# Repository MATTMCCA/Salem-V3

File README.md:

# Salem Version 3

Third Revision of Salem, Capacitive Proximity Sensor.

https://youtu.be/Kz70OKQegTU

---

### Salem was originally designed as a REM Pod competitor. A conscience and lack of follow-though drove me to release the project, for the betterment of *Parapsychology Research*.

(Plus I didn't feel like dealing with *FCC Regulatory Compliance*.... or shipping logistics, customers, pricing, manufacturing, overhead... )

Effective range, depending on placement can vary from 6-10 inches. This is a ballpark estimate from lab testing. I have not had time to carry out a conclusive test to gauge the effective sensing range.

---

### Info

This project is a battery powered capacitive proximity sensor. Some folks believe a device like this will detect paranormal apparitions. **I can not confirm or deny the existence of ghosts. I am also not claiming this device will detect paranormal apparitions, this includes but is not limited too.**

- The Jersey Devil
- The Headless Body of Spiro Agnew
- Ghost
- Demons / Angles
- Batman
- Karma
- UFO's / USO's
- The Chupacabra
- Vampires
- Witches / Wizards
- The SOB that ate my Twix
- Bigfoot / Yeti's
- Tom Cruise
- Most Breads of Cats.
- Bloody Mary
- Unicorns
- Other Benign and Nefarious Mythical Creatures

However devices like this do exist on the market, and consumers use them in an effort to detect the "paranormal".

In full transparency, both the hardware and firmware are included in this repo. Should an individual wish to understand the operation of this device and similar devices, all necessary information is provided.

### Operation Note:

[Further Readings A](https://www.allaboutcircuits.com/technical-articles/introduction-to-capacitive-touch-sensing)

[Further Readings B](https://www.clippercontrols.com/pages/Dielectric-Constant-Values.html)

**I offer no support for this device, it has become a leisurely project.**

---

This project has been added to the hackaday [halloween hackfest](https://hackaday.com/2021/08/10/new-contest-halloween-hackfest/)

### Borrowed works maintain original license.

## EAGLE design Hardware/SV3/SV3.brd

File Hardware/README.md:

# Hardware Assembly 

The following items were purchased to aid in physical assembly.

- [Mounting Tape](https://www.amazon.com/gp/product/B0888DKR92)
- [Stainless Steel Internal Tooth Star Lock Washers](https://www.amazon.com/gp/product/B0794YF3QP/)
- [M3 Stainless Steel 304 Hex Socket Head Cap Bolt](https://www.amazon.com/gp/product/B07VNDFYNQ/)

## Assembly Notes

- `40mm` of `0.5mm x 24mm` mounting tape was used to adhere the battery pack onto the PCB before soldering the battery pack leads.
- `1 M3, lock washer` was placed on the antenna pad
- `1 M3, 5mm bolt` was passed though the lock washer, though the PCB, and screwed into the taped `M3 antenna`.

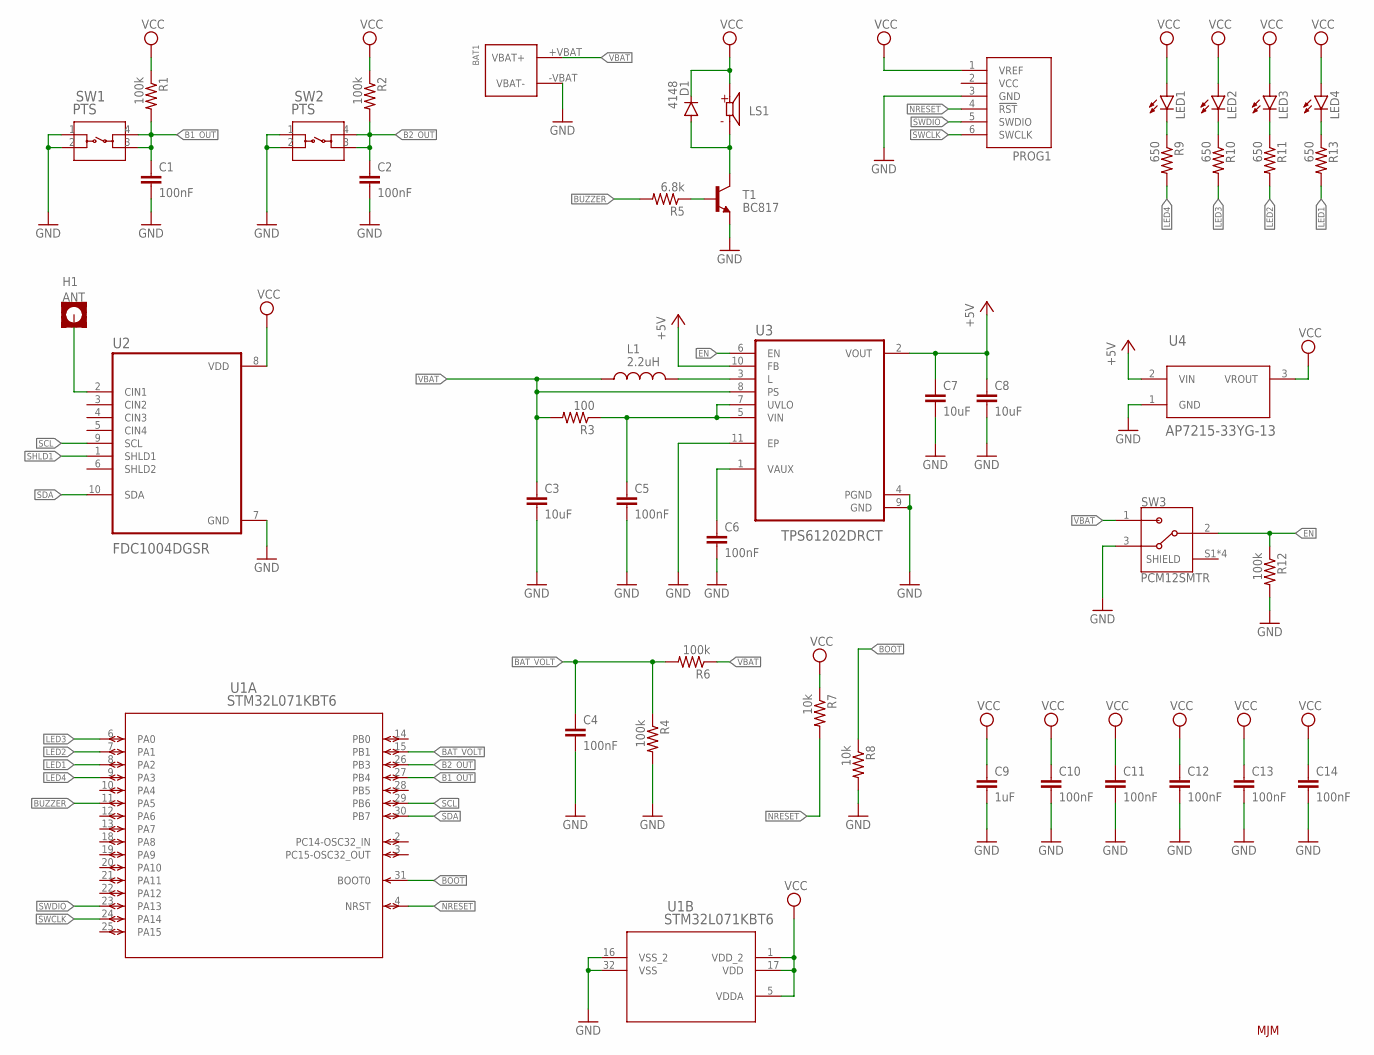
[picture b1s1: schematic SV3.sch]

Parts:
BAT1: 2462_NO_HOLES; 2462_NO-MOUNTING-HOLES
C1, C2, C4, C5, C6, C10, C11, C12, C13, C14: 100nF; C0603
C3, C7, C8: 10uF; C0805
C9: 1uF; C0603
D1: 4148; SOD80C
H1: ANT; 3,3-PAD-SQUARE
L1: 2.2uH; IND_LQH2HPZ2R2MJRL
LED1, LED2, LED3, LED4: LEDCHIPLED_0805; CHIPLED_0805
LS1: CSS-0575A-SMT; CUI_CSS-0575A-SMT
PROG1: 0532610671
R1, R2, R4, R6, R12: 100k; R0603
R3: 100; R0603
R5: 6.8k; R0603
R7, R8: 10k; R0603
R9, R10, R11, R13: 650; R0603
SW1, SW2: PTS; PTS_647_SN50_SMTR2_LFS-M
SW3: PCM12SMTR; SW_PCM12SMTR
T1: BC817; SOT23-BEC
U1: STM32L071KBT6; LQFP32_7X7X1P4
U2: FDC1004DGSR; SOP50P490X110-10N
U3: TPS61202DRCT; VREG_V62/16624-01YE
U4: AP7215-33YG-13; SOT89-3L_DIO-L

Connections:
+5V: C7.1, C8.1, U3.2 (VOUT), U3.10 (FB), U4.2 (VIN)
B: R5.1, T1.B
B1_OUT: C1.1, R1.2, SW1.3, SW1.4, U1.27 (PB4)
B2_OUT: C2.1, R2.2, SW2.3, SW2.4, U1.26 (PB3)
BAT_VOLT: C4.1, R4.1, R6.2, U1.15 (PB1)
BOOT: R8.1, U1.31 (BOOT0)
BUZZER: R5.2, U1.11 (PA5)
C: D1.A, LS1.2 (N), T1.C
EN: R12.1, SW3.2, U3.6 (EN)
GND: BAT1.-VBAT (VBAT-), C1.2, C2.2, C3.2, C4.2, C5.2, C6.2, C7.2, C8.2, C9.2, C10.2, C11.2, C12.2, C13.2, C14.2, PROG1.3 (GND), R4.2, R8.2, R12.2, SW1.1, SW1.2, SW2.1, SW2.2, SW3.3, T1.E, U1.16 (VSS_2), U1.32 (VSS), U2.7 (GND), U3.4 (PGND), U3.9 (GND), U3.11 (EP), U4.1 (GND)
LED1: R13.2, U1.8 (PA2)
LED2: R11.2, U1.7 (PA1)
LED3: R10.2, U1.6 (PA0)
LED4: R9.2, U1.9 (PA3)
unnamed: H1.B3,3, U2.2 (CIN1)
unnamed: C5.1, R3.1, U3.5 (VIN), U3.7 (UVLO)
unnamed: L1.2, U3.3 (L)
unnamed: C6.1, U3.1 (VAUX)
unnamed: LED1.C, R9.1
unnamed: LED2.C, R10.1
unnamed: LED3.C, R11.1
unnamed: LED4.C, R13.1
NRESET: PROG1.4 (!RST), R7.2, U1.4 (NRST)
SCL: U1.29 (PB6), U2.9 (SCL)
SDA: U1.30 (PB7), U2.10 (SDA)
SHLD1: U2.1 (SHLD1)
SWCLK: PROG1.6 (SWCLK), U1.24 (PA14)
SWDIO: PROG1.5 (SWDIO), U1.23 (PA13)
VBAT: BAT1.+VBAT (VBAT+), C3.1, L1.1, R3.2, R6.1, SW3.1, U3.8 (PS)
VCC: C9.1, C10.1, C11.1, C12.1, C13.1, C14.1, D1.C, LED1.A, LED2.A, LED3.A, LED4.A, LS1.1, PROG1.1 (VREF), R1.1, R2.1, R7.1, U1.1 (VDD_2), U1.5 (VDDA), U1.17 (VDD), U2.8 (VDD), U4.3 (VROUT)

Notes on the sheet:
MJM

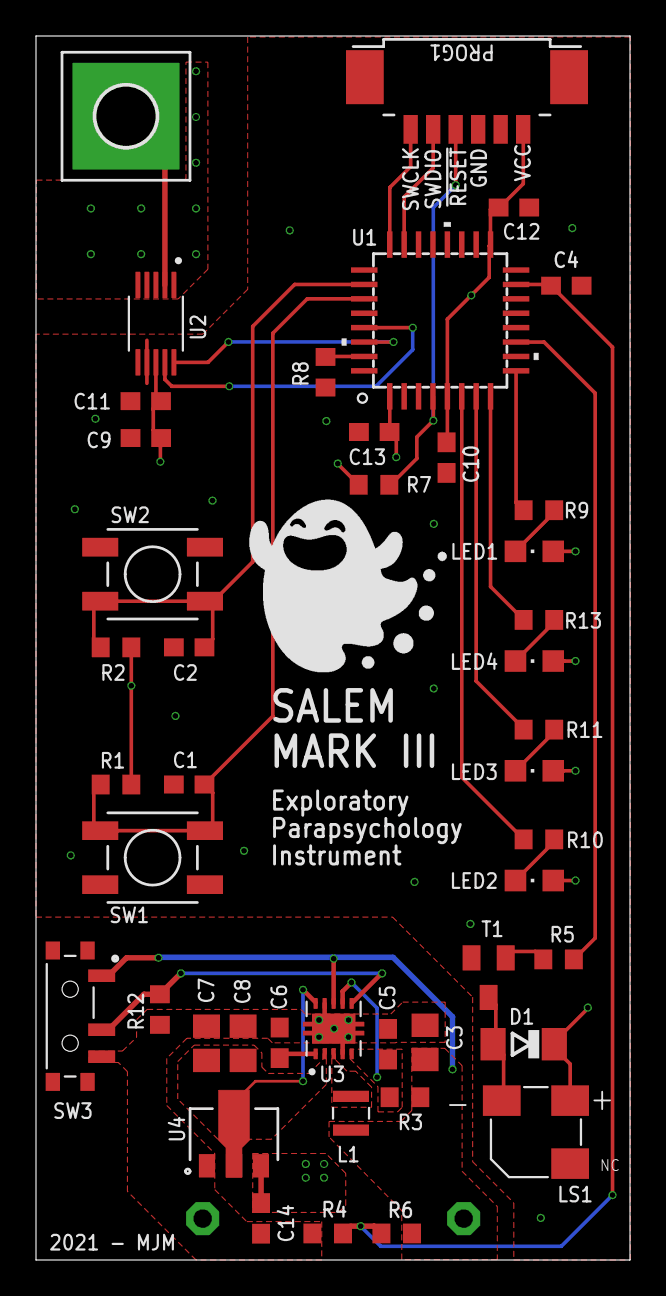
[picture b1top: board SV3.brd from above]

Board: 2 copper layers, 33.0 x 68.0 mm, 46 parts (1 on the bottom side), 29 nets.

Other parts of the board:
U$1: GHOST

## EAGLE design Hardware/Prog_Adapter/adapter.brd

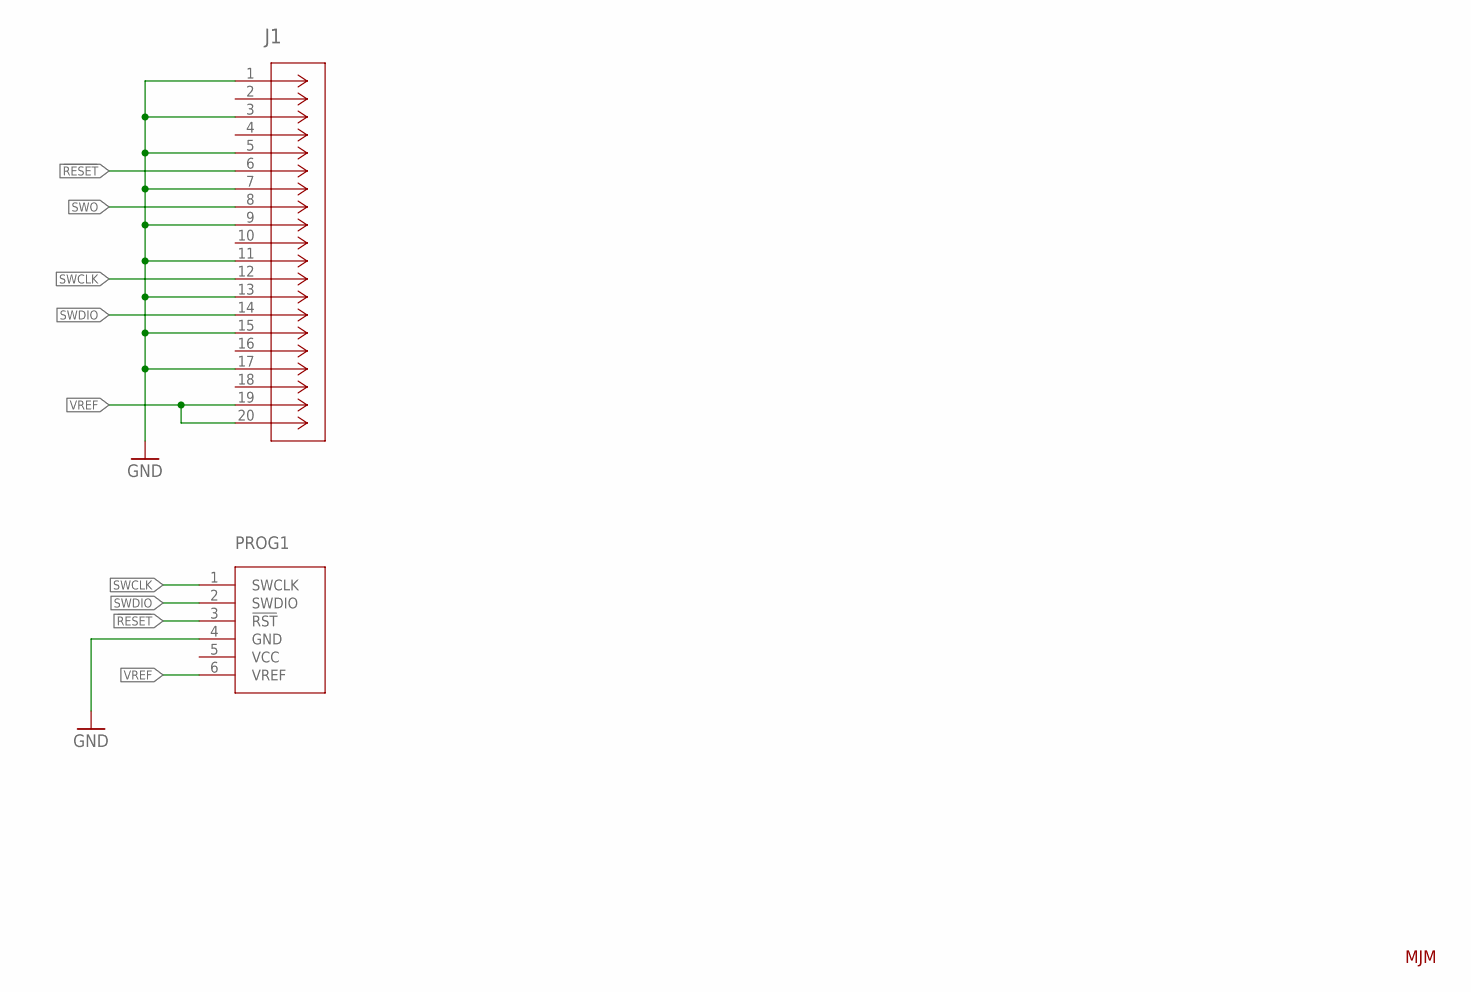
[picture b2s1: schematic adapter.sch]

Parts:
J1: SFH11-PBPC-D10-ST-BK; CONN_SFH11-PBPC-D10-ST-BK_SUL
PROG1: 0532610671_OP; 0532610671

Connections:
!RESET: J1.6, PROG1.3 (!RST)
GND: J1.1, J1.3, J1.5, J1.7, J1.9, J1.11, J1.13, J1.15, J1.17, PROG1.4 (GND)
SWCLK: J1.12, PROG1.1 (SWCLK)
SWDIO: J1.14, PROG1.2 (SWDIO)
SWO: J1.8
VREF: J1.19, J1.20, PROG1.6 (VREF)

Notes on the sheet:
MJM

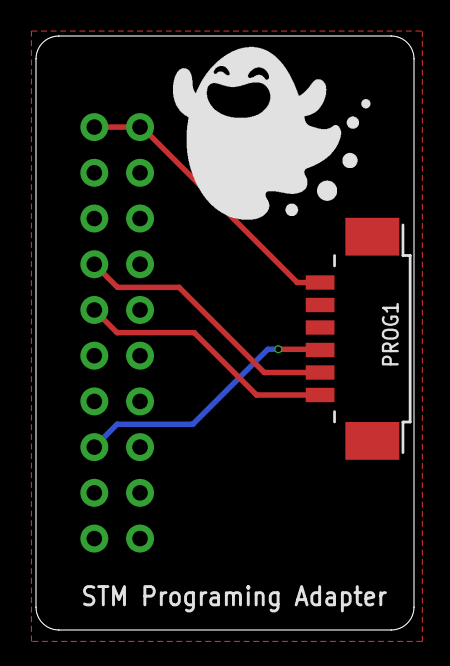
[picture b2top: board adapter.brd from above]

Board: 2 copper layers, 21.0 x 33.0 mm, 3 parts (1 on the bottom side), 5 nets.

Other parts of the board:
U$1: GHOST

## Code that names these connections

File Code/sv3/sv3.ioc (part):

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Mcu.Name=STM32L071K(B-Z)Tx
Mcu.Package=LQFP32
Mcu.UserName=STM32L071KBTx
PA0.GPIOParameters=GPIO_Speed,PinState,GPIO_Label
PA0.GPIO_Label=LED3
PA0.GPIO_Speed=GPIO_SPEED_FREQ_VERY_HIGH
PA0.PinState=GPIO_PIN_SET
PA0.Signal=GPIO_Output
PA1.GPIOParameters=GPIO_Speed,PinState,GPIO_Label
PA1.GPIO_Label=LED2
PA1.GPIO_Speed=GPIO_SPEED_FREQ_VERY_HIGH
PA1.PinState=GPIO_PIN_SET
PA1.Signal=GPIO_Output
PA13.Mode=Serial_Wire
PA13.Signal=SYS_SWDIO
PA14.Mode=Serial_Wire
PA14.Signal=SYS_SWCLK
PA2.GPIOParameters=GPIO_Speed,PinState,GPIO_Label
PA2.GPIO_Label=LED1
PA2.GPIO_Speed=GPIO_SPEED_FREQ_VERY_HIGH
PA2.PinState=GPIO_PIN_SET
PA2.Signal=GPIO_Output
PA3.GPIOParameters=GPIO_Speed,PinState,GPIO_Label
PA3.GPIO_Label=LED4
PA3.GPIO_Speed=GPIO_SPEED_FREQ_VERY_HIGH
PA3.PinState=GPIO_PIN_SET
PA3.Signal=GPIO_Output
PA5.GPIOParameters=GPIO_Speed,GPIO_Label
PA5.GPIO_Label=BUZZER
PA5.GPIO_Speed=GPIO_SPEED_FREQ_VERY_HIGH
PA5.Signal=S_TIM2_CH1
PB1.GPIOParameters=GPIO_Label
PB1.GPIO_Label=VBAT_IN
PB1.Mode=IN9
PB1.Signal=ADC_IN9
PB3.GPIOParameters=GPIO_Label
PB3.GPIO_Label=B2
PB3.Signal=GPIO_Input
PB4.GPIOParameters=GPIO_Label
PB4.GPIO_Label=B1
PB4.Signal=GPIO_Input
PB6.GPIOParameters=GPIO_Pu
PB6.GPIO_Pu=GPIO_PULLUP
PB6.Mode=I2C
PB6.Signal=I2C1_SCL
PB7.GPIOParameters=GPIO_Pu
PB7.GPIO_Pu=GPIO_PULLUP
PB7.Mode=I2C
PB7.Signal=I2C1_SDA
RCC.SYSCLKFreq_VALUE=32000000
RCC.SYSCLKSource=RCC_SYSCLKSOURCE_PLLCLK
board=custom

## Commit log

2021-09-04 public-init
    removed git history
2021-09-04 pic rot
2021-09-04 Update LICENSE
2021-09-04 Added Attribution
2021-09-05 lab vids
2021-09-06 photos

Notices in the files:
parts and their libraries:
COPYRIGHT: Copyright (C) 2018 Accelerated Designs. All rights reserved
